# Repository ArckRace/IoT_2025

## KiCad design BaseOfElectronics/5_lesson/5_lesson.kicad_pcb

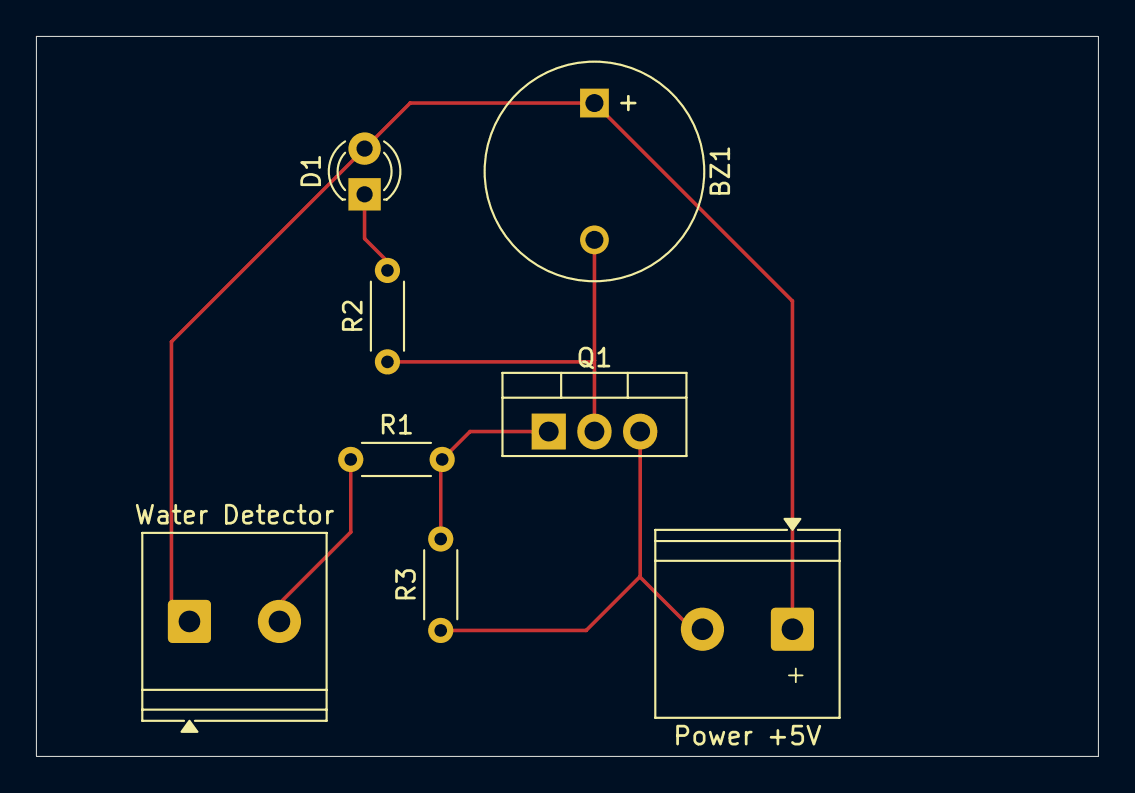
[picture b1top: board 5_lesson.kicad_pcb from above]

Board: 2 copper layers, 59.0 x 40.0 mm, 8 parts (0 on the bottom side), 6 nets.

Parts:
BZ1: Buzzer; MagneticBuzzer_ProSignal_ABI-009-RC
D1: LED; LED_D3.0mm
Power +5V: Vcc; TerminalBlock_Philmore_TB132_1x02_P5.00mm_Horizontal
Q1: IRFZ44N; TO-220-3_Vertical
R1: 10k; R_Axial_DIN0204_L3.6mm_D1.6mm_P5.08mm_Horizontal
R2: 150; R_Axial_DIN0204_L3.6mm_D1.6mm_P5.08mm_Horizontal
R3: 100k; R_Axial_DIN0204_L3.6mm_D1.6mm_P5.08mm_Horizontal
Water Detector: WD; TerminalBlock_Philmore_TB132_1x02_P5.00mm_Horizontal

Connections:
unnamed: BZ1.1 (+), D1.2 (A), Power +5V.1, Water Detector.1
unnamed: BZ1.2 (-), Q1.2 (D), R2.1
unnamed: D1.1 (K), R2.2
unnamed: R1.1, Water Detector.2
unnamed: Power +5V.2, Q1.3 (S), R3.1
unnamed: Q1.1 (G), R1.2, R3.2

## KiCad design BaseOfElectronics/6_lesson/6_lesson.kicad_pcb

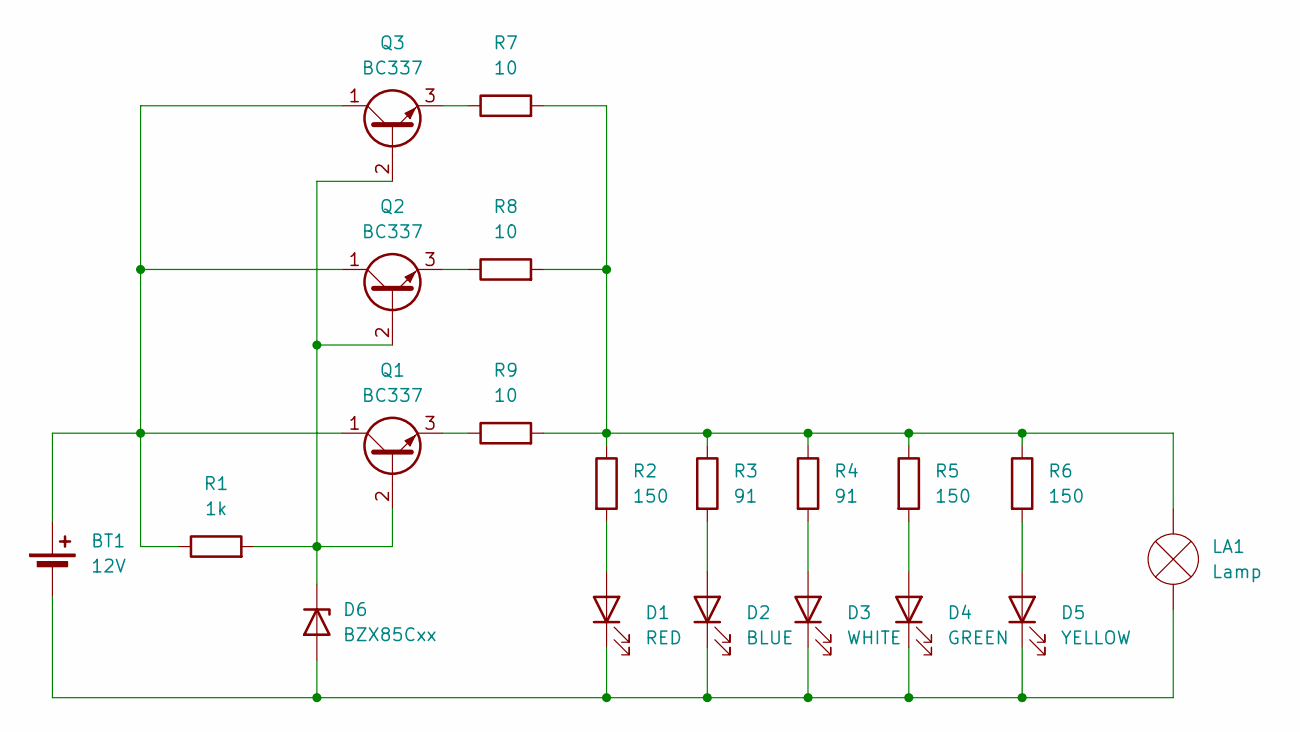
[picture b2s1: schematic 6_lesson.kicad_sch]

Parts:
BT1: 12V; TerminalBlock_TE_282834-2_1x02_P2.54mm_Horizontal
D1: RED; LED_D3.0mm
D2: BLUE; LED_D3.0mm
D3: WHITE; LED_D3.0mm
D4: GREEN; LED_D3.0mm
D5: YELLOW; LED_D3.0mm
D6: BZX85Cxx; D_DO-41_SOD81_P10.16mm_Horizontal
LA1: Lamp; LED_D10.0mm
Q1, Q2, Q3: BC337; TO-92_Inline
R1: 1k; R_Axial_DIN0207_L6.3mm_D2.5mm_P10.16mm_Horizontal
R2, R5, R6: 150; R_Axial_DIN0207_L6.3mm_D2.5mm_P10.16mm_Horizontal
R3, R4: 91; R_Axial_DIN0207_L6.3mm_D2.5mm_P10.16mm_Horizontal
R7, R8, R9: 10; R_Axial_DIN0207_L6.3mm_D2.5mm_P10.16mm_Horizontal

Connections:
unnamed 0: BT1.1 (+), Q1.1 (C), Q2.1 (C), Q3.1 (C), R1.1; also elsewhere on the board
unnamed 1: BT1.2 (-), D1.1 (K), D2.1 (K), D3.1 (K), D4.1 (K), D5.1 (K), D6.1 (A), LA1.1 (-); also elsewhere on the board
unnamed: D1.2 (A), R2.2
unnamed: D2.2 (A), R3.2
unnamed: D3.2 (A), R4.2
unnamed: D4.2 (A), R5.2
unnamed: D5.2 (A), R6.2
unnamed: D6.2 (K), Q1.2 (B), Q2.2 (B), Q3.2 (B), R1.2
unnamed: LA1.2 (+), R2.1, R3.1, R4.1, R5.1, R6.1, R7.2, R8.2, R9.2
unnamed: Q1.3 (E), R9.1
unnamed: Q2.3 (E), R8.1
unnamed: Q3.3 (E), R7.1

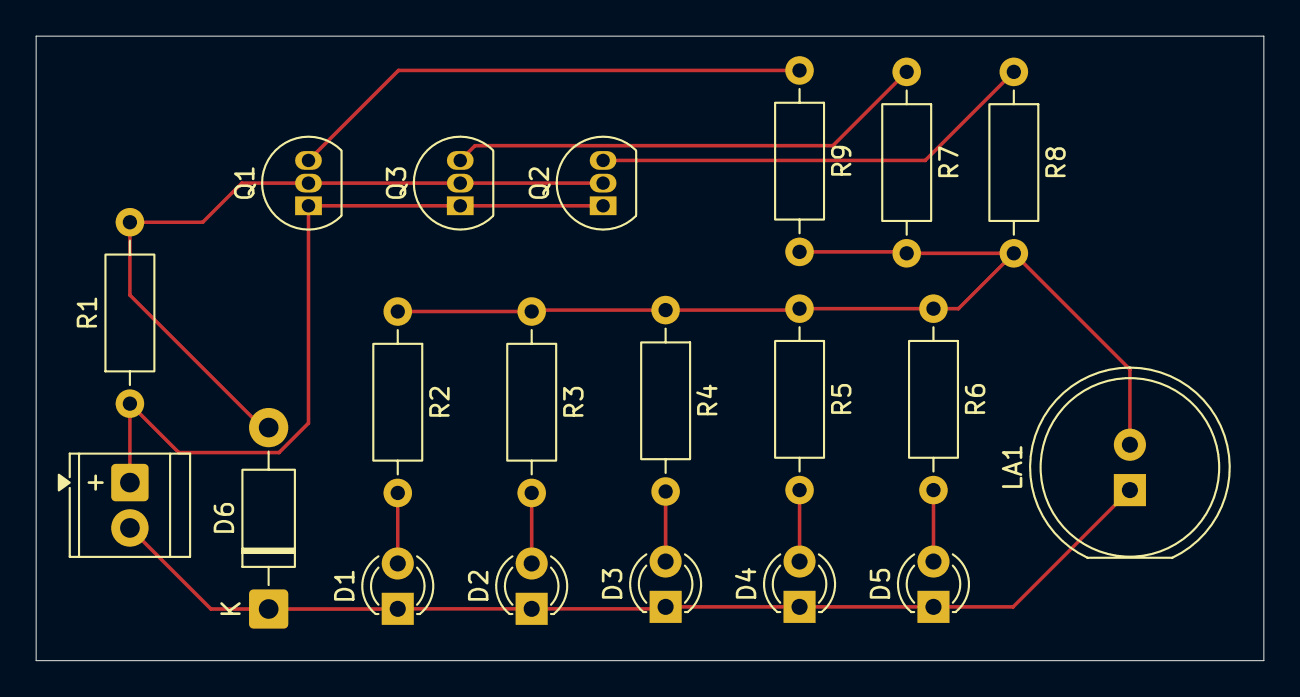
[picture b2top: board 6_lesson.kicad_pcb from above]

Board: 2 copper layers, 68.8 x 35.0 mm, 20 parts (0 on the bottom side), 12 nets.

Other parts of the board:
+: 12V; TerminalBlock_TE_282834-2_1x02_P2.54mm_Horizontal

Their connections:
unnamed 0: +.1 (+); also elsewhere on the board
unnamed 1: +.2 (-); also elsewhere on the board

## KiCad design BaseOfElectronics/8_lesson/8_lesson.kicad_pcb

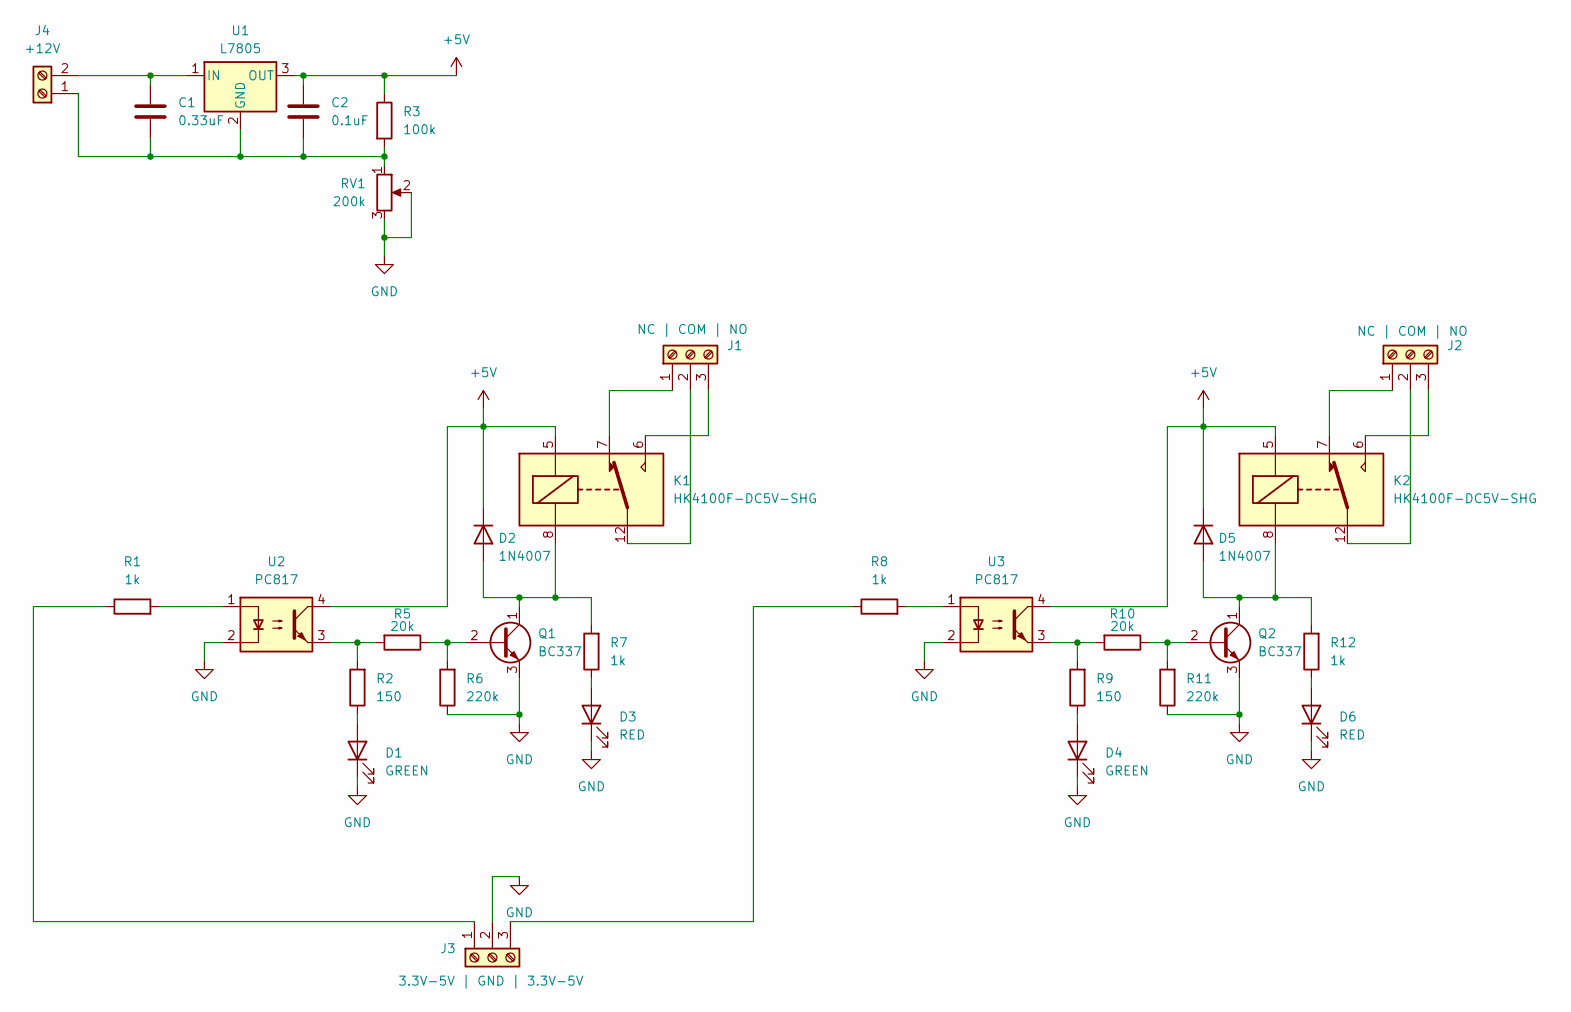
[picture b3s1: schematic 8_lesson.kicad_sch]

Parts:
C1: 0.33uF; C_Radial_D4.0mm_H7.0mm_P1.50mm
C2: 0.1uF; C_Disc_D3.0mm_W2.0mm_P2.50mm
D1, D4: GREEN; LED_D3.0mm
D2, D5: 1N4007; D_DO-41_SOD81_P10.16mm_Horizontal
D3, D6: RED; LED_D3.0mm
J1, J2: NC | COM | NO; TerminalBlock_MaiXu_MX126-5.0-03P_1x03_P5.00mm
J3: 3.3V-5V | GND | 3.3V-5V; TerminalBlock_MaiXu_MX126-5.0-03P_1x03_P5.00mm
J4: +12V; TerminalBlock_MaiXu_MX126-5.0-02P_1x02_P5.00mm
K1, K2: HK4100F-DC5V-SHG; Relay_SPDT_HJR-4102
Q1, Q2: BC337; TO-92_Inline
R1, R7, R8, R12: 1k; R_Axial_DIN0207_L6.3mm_D2.5mm_P7.62mm_Horizontal
R2, R9: 150; R_Axial_DIN0207_L6.3mm_D2.5mm_P7.62mm_Horizontal
R3: 100k; R_Axial_DIN0207_L6.3mm_D2.5mm_P7.62mm_Horizontal
R5, R10: 20k; R_Axial_DIN0207_L6.3mm_D2.5mm_P7.62mm_Horizontal
R6, R11: 220k; R_Axial_DIN0207_L6.3mm_D2.5mm_P7.62mm_Horizontal
RV1: 200k; Potentiometer_Bourns_3296W_Vertical
U1: L7805; TO-220-3_Vertical
U2, U3: PC817; DIP-4_W7.62mm

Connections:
+5V: C2.1, D2.1 (K), D5.1 (K), K1.5, K2.5, R3.1, U1.3 (OUT), U2.4, U3.4
GND: D1.1 (K), D3.1 (K), D4.1 (K), D6.1 (K), J3.2, Q1.3 (E), Q2.3 (E), R6.1, R11.1, RV1.2, RV1.3, U2.2, U3.2
unnamed: D1.2 (A), R2.1
unnamed: D2.2 (A), K1.8, Q1.1 (C), R7.2
unnamed: D3.2 (A), R7.1
unnamed: D4.2 (A), R9.1
unnamed: D5.2 (A), K2.8, Q2.1 (C), R12.2
unnamed: D6.2 (A), R12.1
unnamed: J1.1, K1.7
unnamed: J1.2, K1.12
unnamed: J1.3, K1.6
unnamed: J2.1, K2.7
unnamed: J2.2, K2.12
unnamed: J2.3, K2.6
unnamed: J3.1, R1.1
unnamed: J3.3, R8.1
unnamed: C1.2, C2.2, J4.1, R3.2, RV1.1, U1.2 (GND)
unnamed: C1.1, J4.2, U1.1 (IN)
unnamed: Q1.2 (B), R5.1, R6.2
unnamed: Q2.2 (B), R10.1, R11.2
unnamed: R1.2, U2.1
unnamed: R2.2, R5.2, U2.3
unnamed: R8.2, U3.1
unnamed: R9.2, R10.2, U3.3

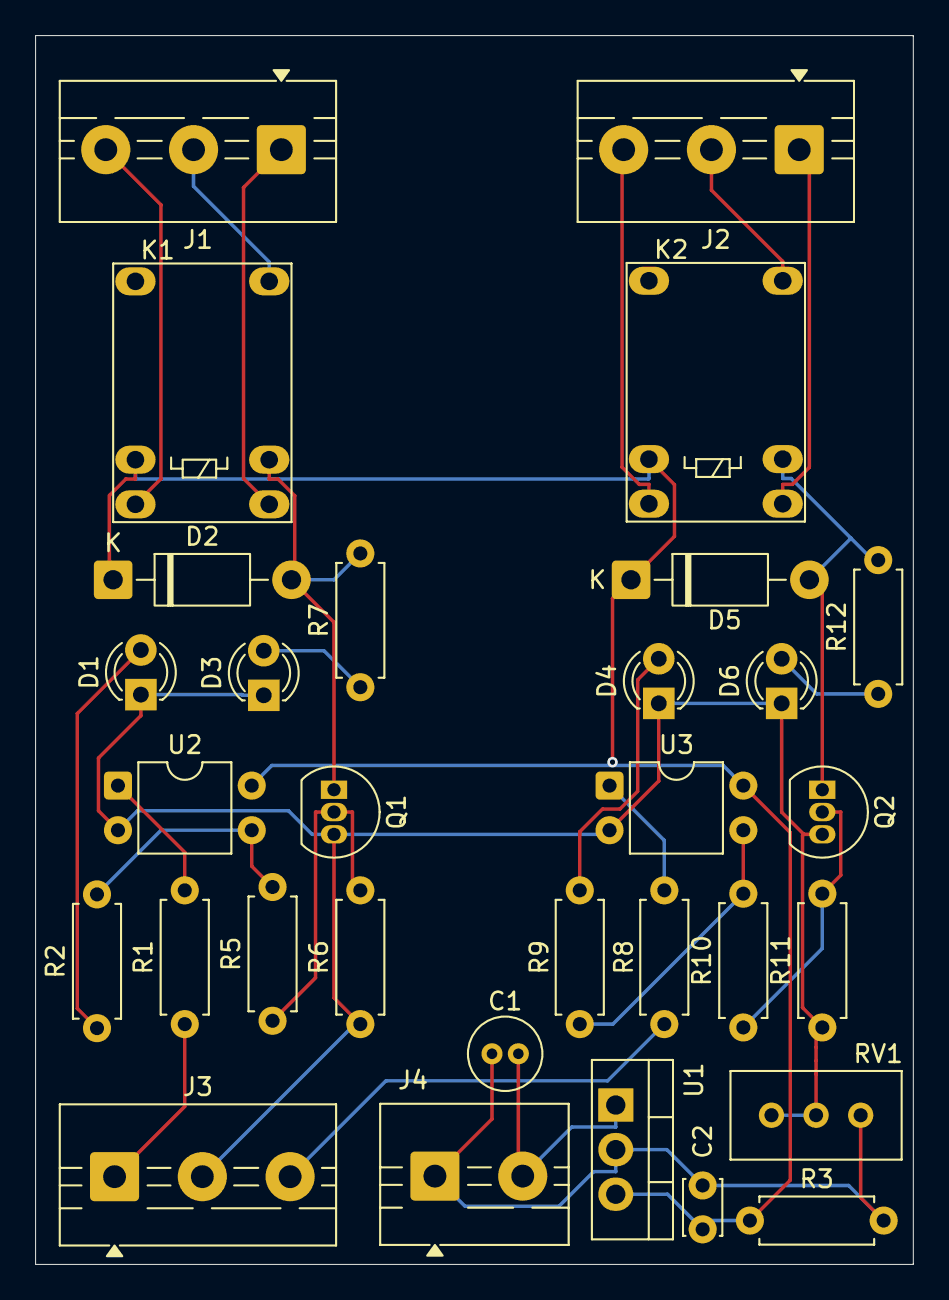
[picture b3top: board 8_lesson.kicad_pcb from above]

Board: 2 copper layers, 50.0 x 70.0 mm, 31 parts (0 on the bottom side), 24 nets.

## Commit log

2025-02-05 First homeworks
2025-02-09 Add .gitignore file
2025-02-09 Add Homework 2
2025-02-11 Add homework 3 and 4
2025-02-20 Added homework 5
2025-02-22 Added HomeWork 6
2025-02-22 C20 dont work
2025-02-27 Add Homework 7
2025-03-06 Added HomeWork_8
2025-03-14 Added HomeWork_9
2025-03-26 Added HomeWork_10
2025-04-02 Add first step of Course project
2025-04-12 Add new feature in program "Temperature"
2025-04-17 Add Course work report
2025-05-16 Add electronics and change dir for BaseOf C
2025-06-17 Add 2 3 4 HomeWork
2026-03-23 add new
